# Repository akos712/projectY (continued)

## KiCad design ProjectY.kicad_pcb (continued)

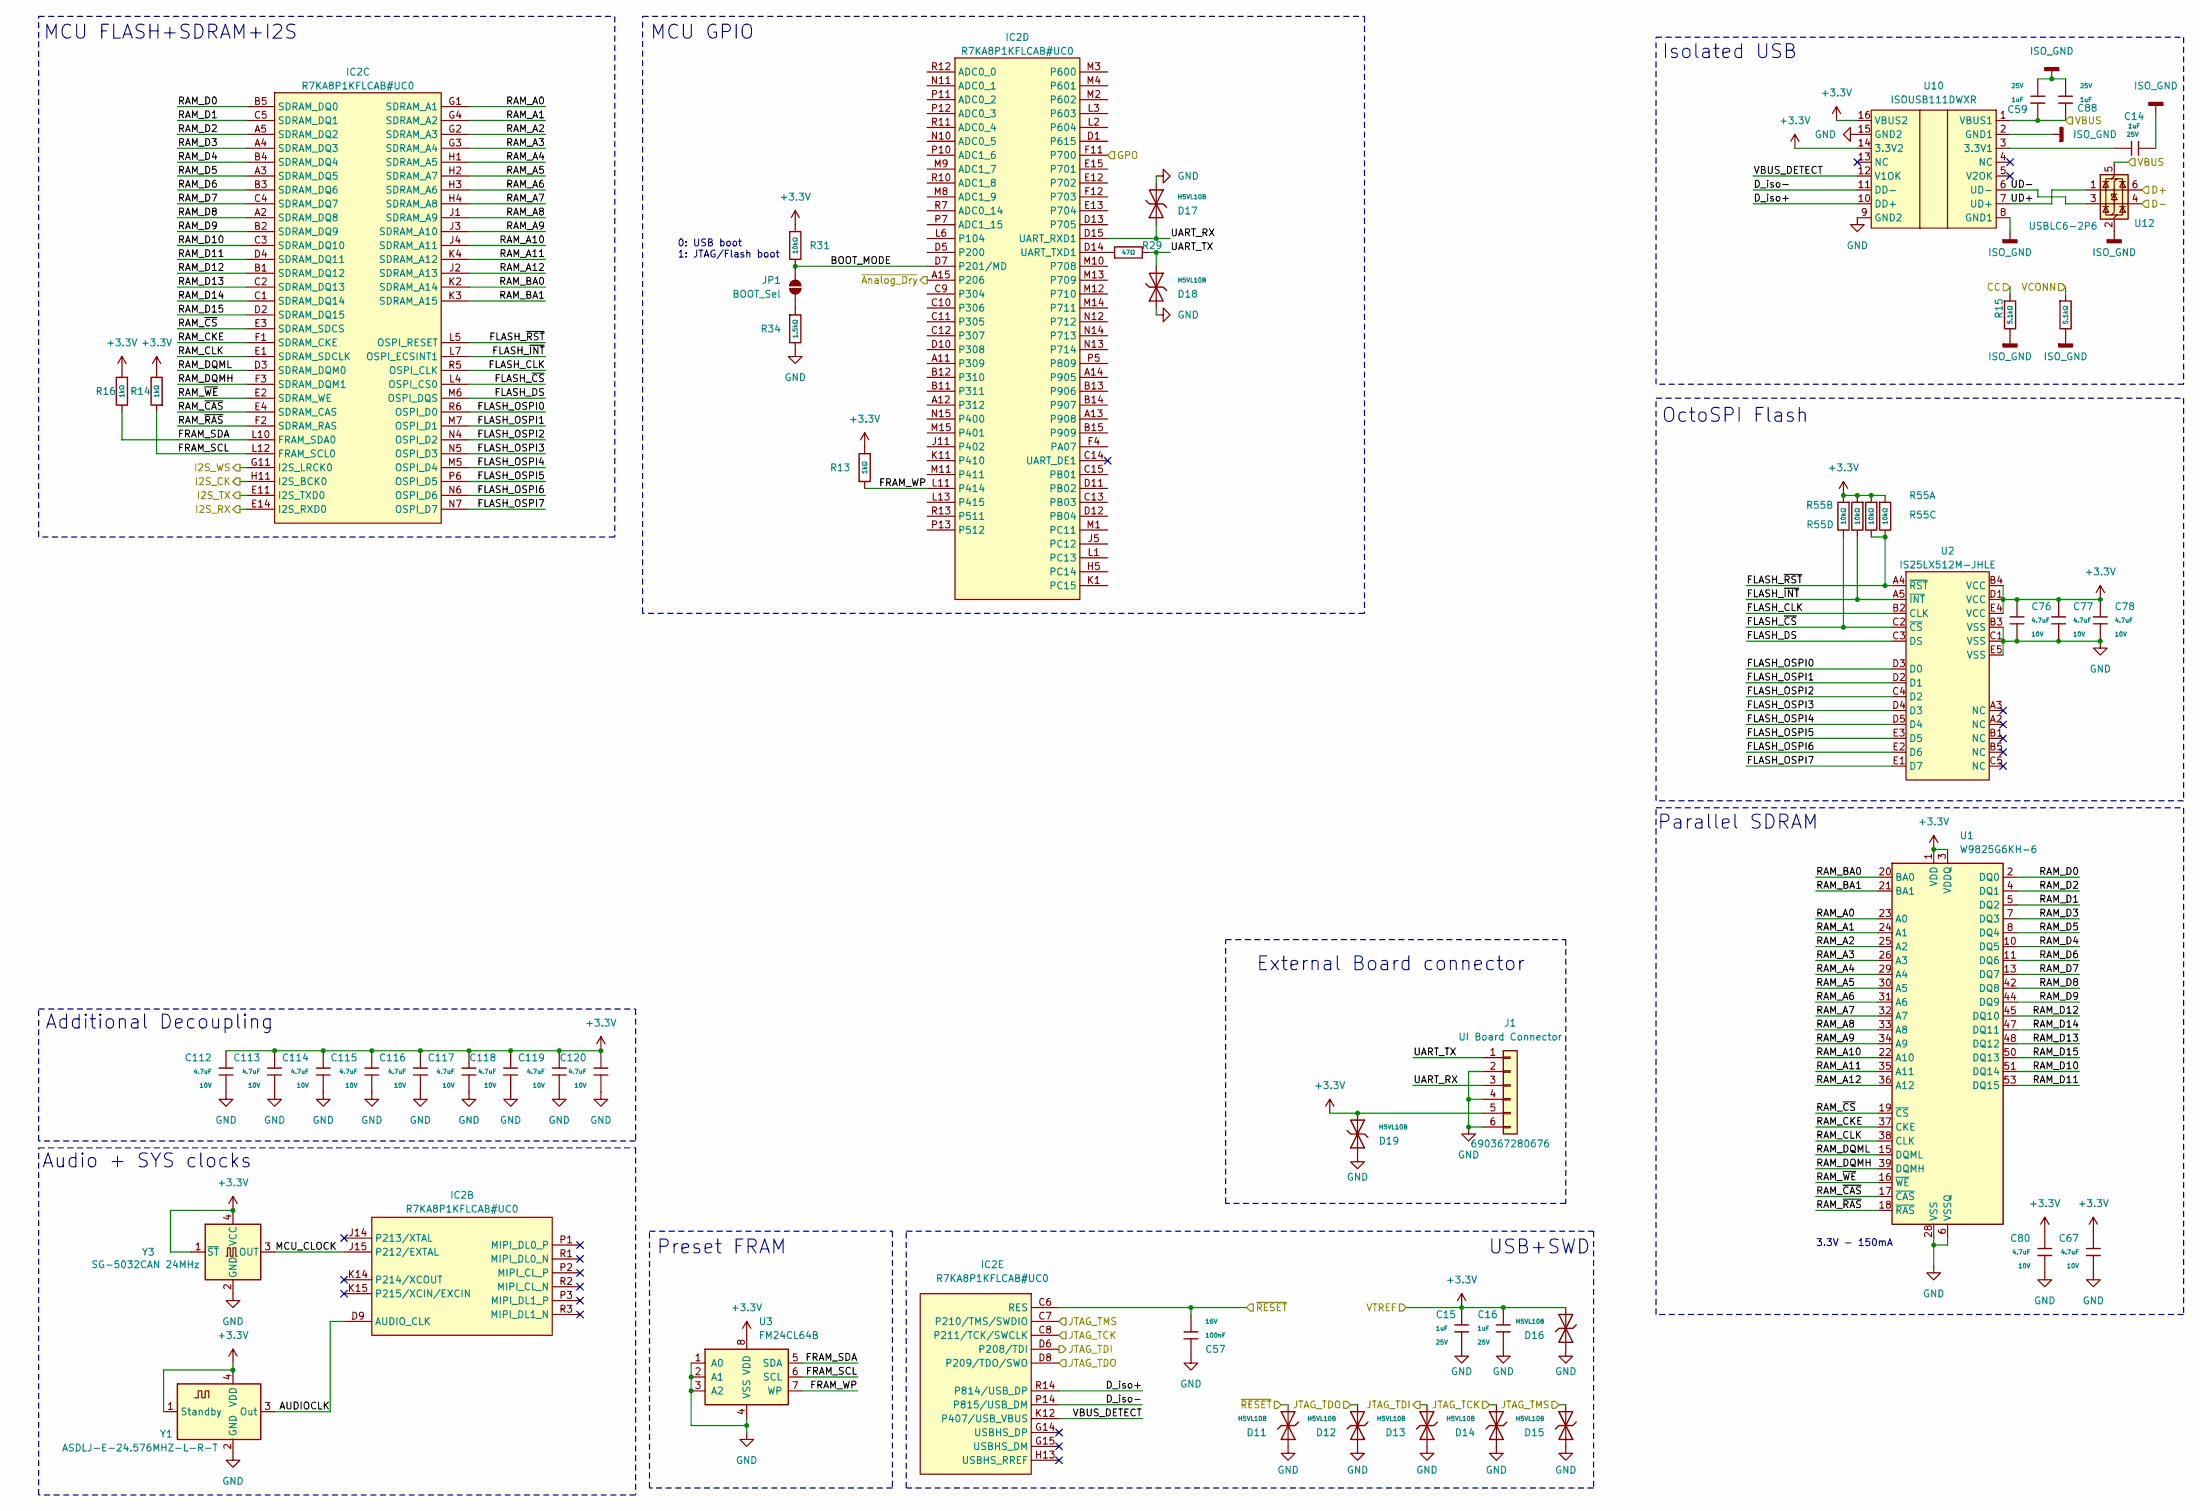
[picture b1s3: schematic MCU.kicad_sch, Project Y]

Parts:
C14, C15, C16, C59, C88: 1uF; C_0402; Voltage Rated 25V; Tolerance ±10%; Part CL05A105KA5NQNC; LCSC C52923
C57: 100nF; C_0402; Voltage Rated 16V; Tolerance ±10%; Part CL05B104KO5NNNC; LCSC C1525
C67, C76, C77, C78, C80, C112, C113, C114, C115, C116, C117, C118, C119, C120: 4.7uF; C_0402; Voltage Rated 10V; Tolerance ±20%; Part CL05A475MP5NRNC; LCSC C23733
D11, D12, D13, D14, D15, D16, D17, D18, D19: H5VL10B; D_DFN1006-2L; Clamping Voltage@Ipp 10V; Breakdown Voltage (VBR) 5.6V; Part H5VL10B; LCSC C7420372
IC2: R7KA8P1KFLCAB#UC0; BGA-225_15x15_11.0x11.0mm; Manufacturer_Part_Number R7KA8P1KFLCAB#UC0
J1: UI Board Connector; J_Wurth_WR-MM_690367280676
JP1: BOOT_Sel; SolderJumper-2_P1.3mm_Open_RoundedPad1.0x1.5mm
R1, R15: 5.1kΩ; R_0402; Overload Voltage (Max) 50V; Tolerance ±1%; Part 0402WGF5101TCE; LCSC C25905
R13, R14, R16: 1kΩ; R_0402; Overload Voltage (Max) 50V; Tolerance ±1%; Part 0402WGF1001TCE; LCSC C11702
R29: 47Ω; R_0402; Overload Voltage (Max) 50V; Tolerance ±1%; Part 0402WGF470JTCE; LCSC C25118
R31: 10kΩ; R_0402; Overload Voltage (Max) 50V; Tolerance ±1%; Part 0402WGF1002TCE; LCSC C25744
R34: 1.5kΩ; R_0402; Overload Voltage (Max) 50V; Tolerance ±1%; Part 0402WGF1501TCE; LCSC C25867
R55: 10kΩ; R_0402x4; Tolerance ±5%; Part 4D02WGJ0103TCE; LCSC C25725
U1: W9825G6KH-6; TSOP-II-54_22.2x10.16mm_P0.8mm; LCSC C97572
U2: IS25LX512M-JHLE; BGA-24_6x8mm_Layout5x5_P1.0mm
U3: FM24CL64B; SOIC-8_3.9x4.9mm_P1.27mm; LCSC C9829
U10: ISOUSB111DWXR; SOIC16_DW_TEX-L
U12: USBLC6-2P6; SOT-666
Y1: ASDLJ-E-24.576MHZ-L-R-T; Oscillator_SMD_Abracon_ASDMB-4Pin_2.5x2.0mm
Y3: SG-5032CAN 24MHz; Oscillator_SMD_SeikoEpson_SG8002LB-4Pin_5.0x3.2mm

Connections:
+3.3V: C15.2, C16.2, C67.1, C76.1, C77.1, C78.1, C80.1, C112.1, C113.1, C114.1, C115.1, C116.1, C117.1, C118.1, C119.1, C120.1, D16.1, D19.1, J1.5, R13.1, R14.2, R16.1, R31.1, R55.1, R55.2, R55.3, R55.4, U1.1 (VDD), U1.3 (VDDQ), U1.9 (VDDQ), U1.14 (VDD), U1.27 (VDD), U1.43 (VDDQ), U1.49 (VDDQ), U2.B4 (VCC), U2.D1 (VCC), U2.E4 (VCC), U3.8 (VDD), U10.14 (3.3V2), U10.16 (VBUS2), Y1.1 (Standby), Y1.4 (VDD), Y3.1 (~ST), Y3.4 (VCC); also elsewhere on the board
/Analog Audio/GP0: IC2.F11 (P700); also elsewhere on the board
/Analog Audio/I2S_CK: IC2.H11 (I2S_BCK0); also elsewhere on the board
/Analog Audio/I2S_RX: IC2.E14 (I2S_RXD0); also elsewhere on the board
/Analog Audio/I2S_TX: IC2.E11 (I2S_TXD0); also elsewhere on the board
/Analog Audio/I2S_WS: IC2.G11 (I2S_LRCK0); also elsewhere on the board
/Analog Audio/~Analog_Dry: IC2.A15 (P206); also elsewhere on the board
/DSP/AUDIOCLK: IC2.D9 (AUDIO_CLK), Y1.3 (Out)
/DSP/BOOT_MODE: IC2.D7 (P201/MD), JP1.2 (B), R31.2
/DSP/CC: R15.1; also elsewhere on the board
/DSP/D+: U12.6 (I/O1); also elsewhere on the board
/DSP/D-: U12.4 (I/O2); also elsewhere on the board
/DSP/D_iso+: IC2.R14 (P814/USB_DP), U10.10 (DD+)
/DSP/D_iso-: IC2.P14 (P815/USB_DM), U10.11 (DD-)
/DSP/FLASH_CLK: IC2.R5 (OSPI_CLK), U2.B2 (CLK)
/DSP/FLASH_DS: IC2.M6 (OSPI_DQS), U2.C3 (DS)
/DSP/FLASH_OSPI0: IC2.R6 (OSPI_D0), U2.D3 (D0)
/DSP/FLASH_OSPI1: IC2.M7 (OSPI_D1), U2.D2 (D1)
/DSP/FLASH_OSPI2: IC2.N4 (OSPI_D2), U2.C4 (D2)
/DSP/FLASH_OSPI3: IC2.N5 (OSPI_D3), U2.D4 (D3)
/DSP/FLASH_OSPI4: IC2.M5 (OSPI_D4), U2.D5 (D4)
/DSP/FLASH_OSPI5: IC2.P6 (OSPI_D5), U2.E3 (D5)
/DSP/FLASH_OSPI6: IC2.N6 (OSPI_D6), U2.E2 (D6)
/DSP/FLASH_OSPI7: IC2.N7 (OSPI_D7), U2.E1 (D7)
/DSP/FLASH_~CS: IC2.L4 (OSPI_CS0), R55.5, U2.C2 (~CS)
/DSP/FLASH_~INT: IC2.L7 (OSPI_ECSINT1), R55.8, U2.A5 (~INT)
/DSP/FLASH_~RST: IC2.L5 (OSPI_RESET), R55.6, R55.7, U2.A4 (~RST)
/DSP/FRAM_SCL: IC2.L12 (FRAM_SCL0), R14.1, U3.6 (SCL)
/DSP/FRAM_SDA: IC2.L10 (FRAM_SDA0), R16.2, U3.5 (SDA)
/DSP/FRAM_WP: IC2.L11 (P414), R13.2, U3.7 (WP)
/DSP/JTAG_TCK: D14.1, IC2.C8 (P211/TCK/SWCLK); also elsewhere on the board
/DSP/JTAG_TDI: D13.1, IC2.D6 (P208/TDI); also elsewhere on the board
/DSP/JTAG_TDO: D12.1, IC2.D8 (P209/TDO/SWO); also elsewhere on the board
/DSP/JTAG_TMS: D15.1, IC2.C7 (P210/TMS/SWDIO); also elsewhere on the board
/DSP/MCU_CLOCK: IC2.J15 (P212/EXTAL), Y3.3 (OUT)
/DSP/RAM_A0: IC2.G1 (SDRAM_A1), U1.23 (A0)
/DSP/RAM_A1: IC2.G4 (SDRAM_A2), U1.24 (A1)
/DSP/RAM_A2: IC2.G2 (SDRAM_A3), U1.25 (A2)
/DSP/RAM_A3: IC2.G3 (SDRAM_A4), U1.26 (A3)
/DSP/RAM_A4: IC2.H1 (SDRAM_A5), U1.29 (A4)
/DSP/RAM_A5: IC2.H2 (SDRAM_A7), U1.30 (A5)
/DSP/RAM_A6: IC2.H3 (SDRAM_A6), U1.31 (A6)
/DSP/RAM_A7: IC2.H4 (SDRAM_A8), U1.32 (A7)
/DSP/RAM_A8: IC2.J1 (SDRAM_A9), U1.33 (A8)
/DSP/RAM_A9: IC2.J3 (SDRAM_A10), U1.34 (A9)
/DSP/RAM_A10: IC2.J4 (SDRAM_A11), U1.22 (A10)
/DSP/RAM_A11: IC2.K4 (SDRAM_A12), U1.35 (A11)
/DSP/RAM_A12: IC2.J2 (SDRAM_A13), U1.36 (A12)
/DSP/RAM_BA0: IC2.K2 (SDRAM_A14), U1.20 (BA0)
/DSP/RAM_BA1: IC2.K3 (SDRAM_A15), U1.21 (BA1)
/DSP/RAM_CKE: IC2.F1 (SDRAM_CKE), U1.37 (CKE)
/DSP/RAM_CLK: IC2.E1 (SDRAM_SDCLK), U1.38 (CLK)
/DSP/RAM_D0: IC2.B5 (SDRAM_DQ0), U1.2 (DQ0)
/DSP/RAM_D1: IC2.C5 (SDRAM_DQ1), U1.5 (DQ2)
/DSP/RAM_D2: IC2.A5 (SDRAM_DQ2), U1.4 (DQ1)
/DSP/RAM_D3: IC2.A4 (SDRAM_DQ3), U1.7 (DQ3)
/DSP/RAM_D4: IC2.B4 (SDRAM_DQ4), U1.10 (DQ5)
/DSP/RAM_D5: IC2.A3 (SDRAM_DQ5), U1.8 (DQ4)
/DSP/RAM_D6: IC2.B3 (SDRAM_DQ6), U1.11 (DQ6)
/DSP/RAM_D7: IC2.C4 (SDRAM_DQ7), U1.13 (DQ7)
/DSP/RAM_D8: IC2.A2 (SDRAM_DQ8), U1.42 (DQ8)
/DSP/RAM_D9: IC2.B2 (SDRAM_DQ9), U1.44 (DQ9)
/DSP/RAM_D10: IC2.C3 (SDRAM_DQ10), U1.51 (DQ14)
/DSP/RAM_D11: IC2.D4 (SDRAM_DQ11), U1.53 (DQ15)
/DSP/RAM_D12: IC2.B1 (SDRAM_DQ12), U1.45 (DQ10)
/DSP/RAM_D13: IC2.C2 (SDRAM_DQ13), U1.48 (DQ12)
/DSP/RAM_D14: IC2.C1 (SDRAM_DQ14), U1.47 (DQ11)
/DSP/RAM_D15: IC2.D2 (SDRAM_DQ15), U1.50 (DQ13)
/DSP/RAM_DQMH: IC2.F3 (SDRAM_DQM1), U1.39 (DQMH)
/DSP/RAM_DQML: IC2.D3 (SDRAM_DQM0), U1.15 (DQML)
/DSP/RAM_~CAS: IC2.E4 (SDRAM_CAS), U1.17 (~CAS)
/DSP/RAM_~CS: IC2.E3 (SDRAM_SDCS), U1.19 (~CS)
/DSP/RAM_~RAS: IC2.F2 (SDRAM_RAS), U1.18 (~RAS)
/DSP/RAM_~WE: IC2.E2 (SDRAM_WE), U1.16 (~WE)
/DSP/UART_RX: D17.2, IC2.D15 (UART_RXD1), J1.3
/DSP/UART_TX: D18.1, J1.1, R29.2
/DSP/UD+: U10.7 (UD+), U12.1 (I/O1)
/DSP/UD-: U10.6 (UD-), U12.3 (I/O2)
/DSP/VBUS: C59.1, C88.1, U10.1 (VBUS1), U12.5 (VBUS); also elsewhere on the board
/DSP/VBUS_DETECT: IC2.K12 (P407/USB_VBUS), U10.12 (V1OK)
/DSP/VCONN: R1.1; also elsewhere on the board
/DSP/~RESET: C57.2, D11.1, IC2.C6 (RES); also elsewhere on the board
GND: C15.1, C16.1, C57.1, C67.2, C76.2, C77.2, C78.2, C80.2, C112.2, C113.2, C114.2, C115.2, C116.2, C117.2, C118.2, C119.2, C120.2, D11.2, D12.2, D13.2, D14.2, D15.2, D16.2, D17.1, D18.2, D19.2, J1.2, J1.4, J1.6, R34.2, U1.6 (VSSQ), U1.12 (VSSQ), U1.28 (VSS), U1.41 (VSS), U1.46 (VSSQ), U1.52 (VSSQ), U1.54 (VSS), U2.B3 (VSS), U2.C1 (VSS), U2.E5 (VSS), U3.1 (A0), U3.2 (A1), U3.3 (A2), U3.4 (VSS), U10.9 (GND2), U10.15 (GND2), Y1.2 (GND), Y3.2 (GND); also elsewhere on the board
ISO_GND: C14.2, C59.2, C88.2, R1.2, R15.2, U10.2 (GND1), U10.8 (GND1), U12.2 (GND); also elsewhere on the board
unnamed: IC2.D14 (UART_TXD1), R29.1
unnamed: JP1.1 (A), R34.1
unnamed: C14.1, U10.3 (3.3V1)

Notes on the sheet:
OctoSPI Flash
Isolated USB
MCU GPIO
Parallel SDRAM
MCU FLASH+SDRAM+I2S
3.3V - 150mA
0: USB boot 1: JTAG/Flash boot
External Board connector
Audio + SYS clocks
USB+SWD
Preset FRAM
Additional Decoupling

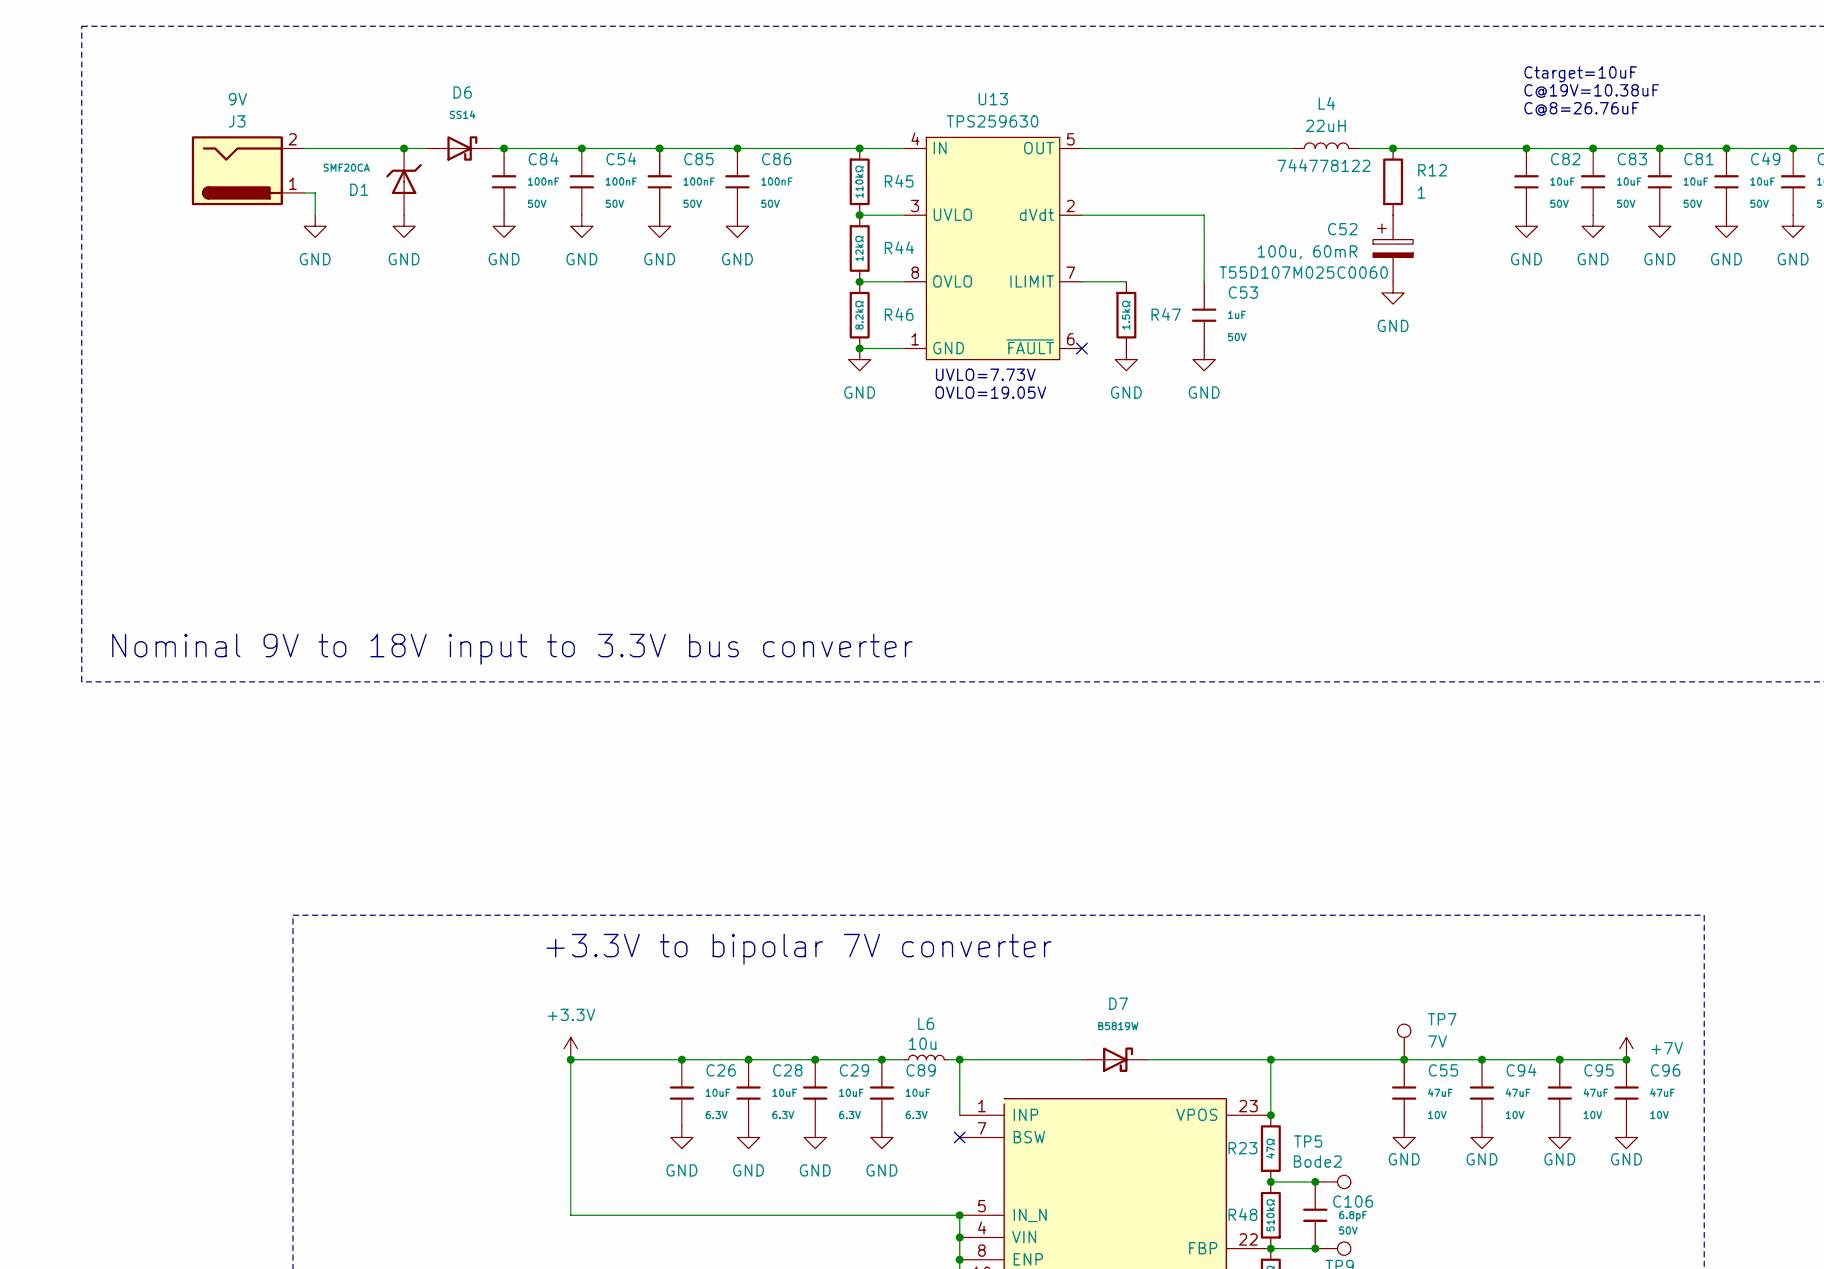
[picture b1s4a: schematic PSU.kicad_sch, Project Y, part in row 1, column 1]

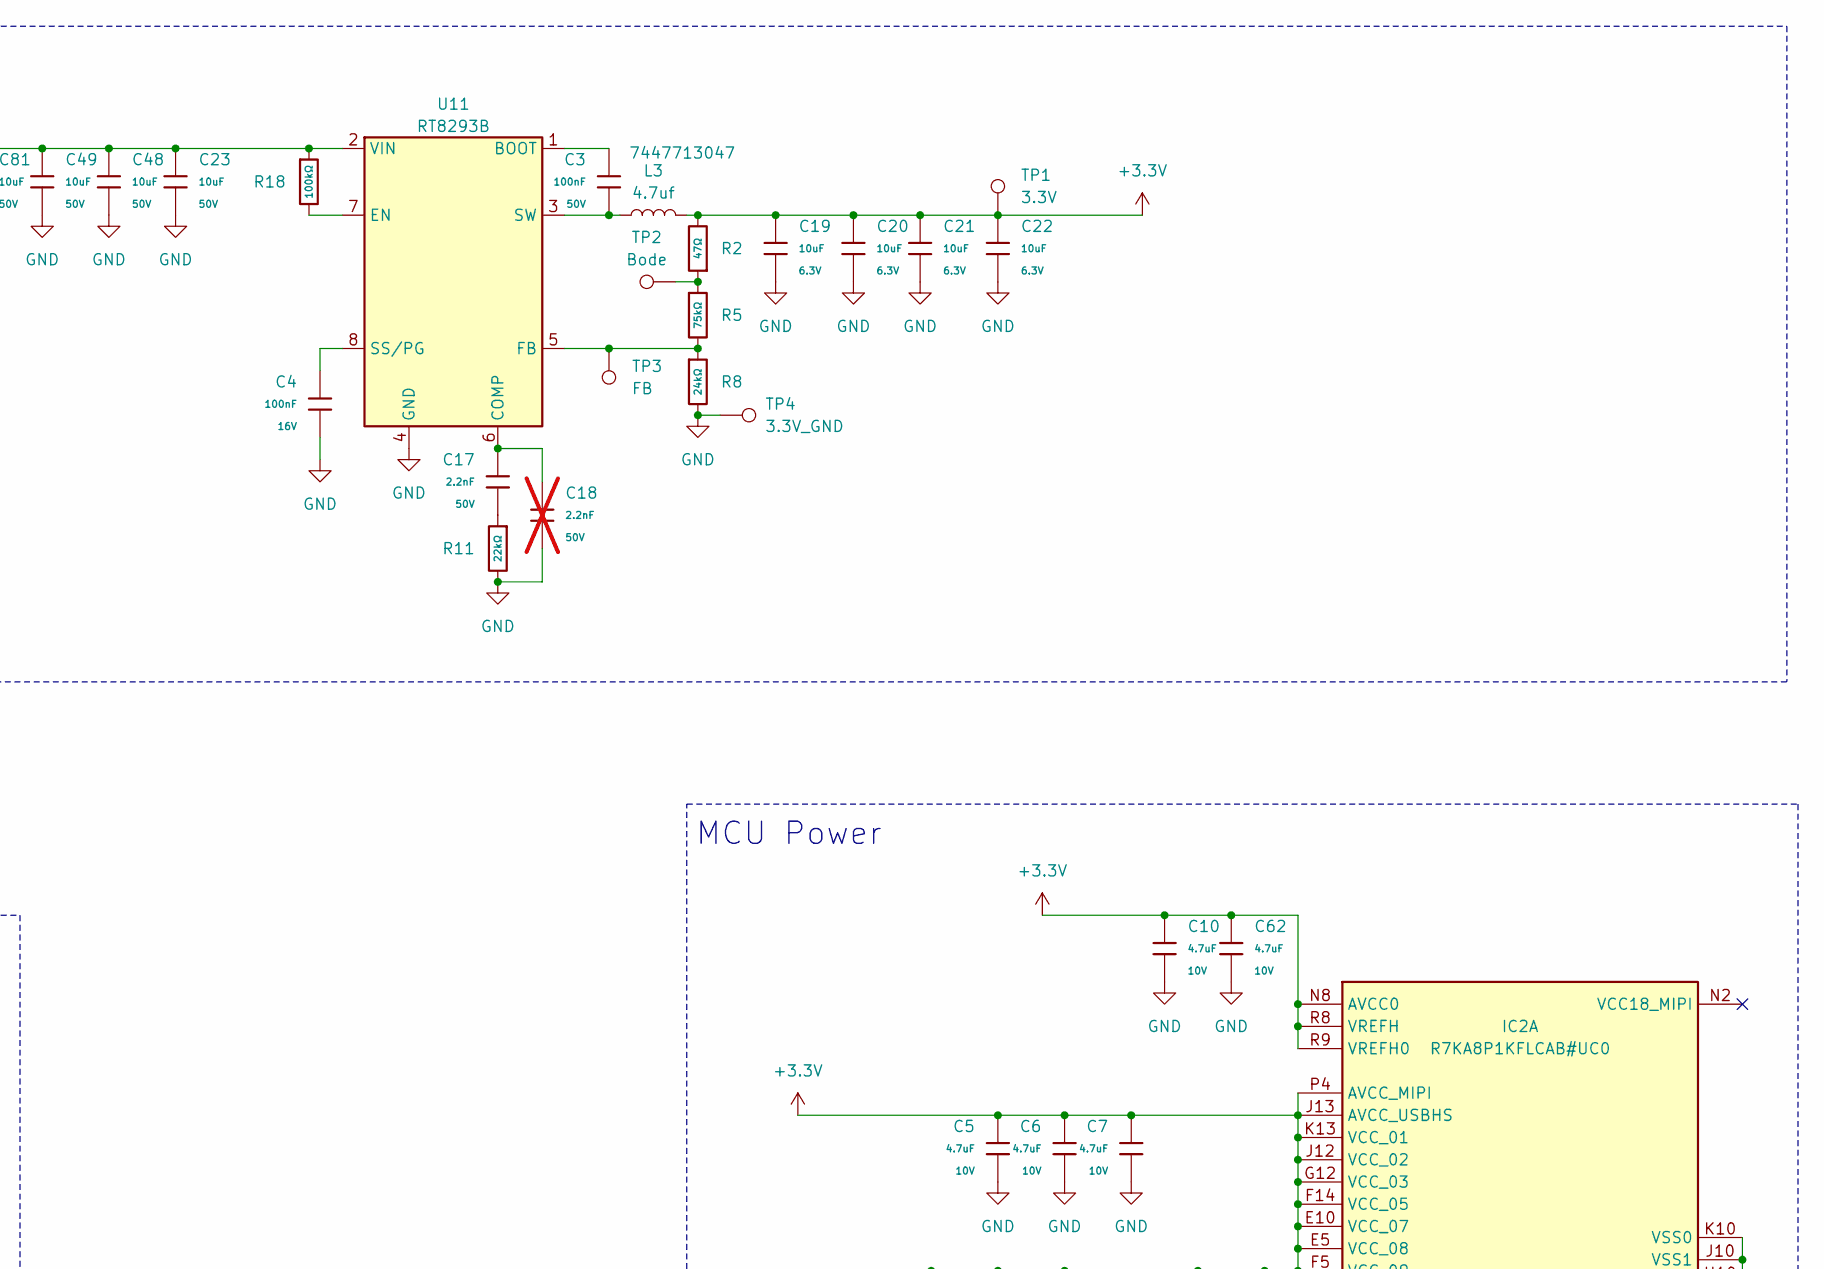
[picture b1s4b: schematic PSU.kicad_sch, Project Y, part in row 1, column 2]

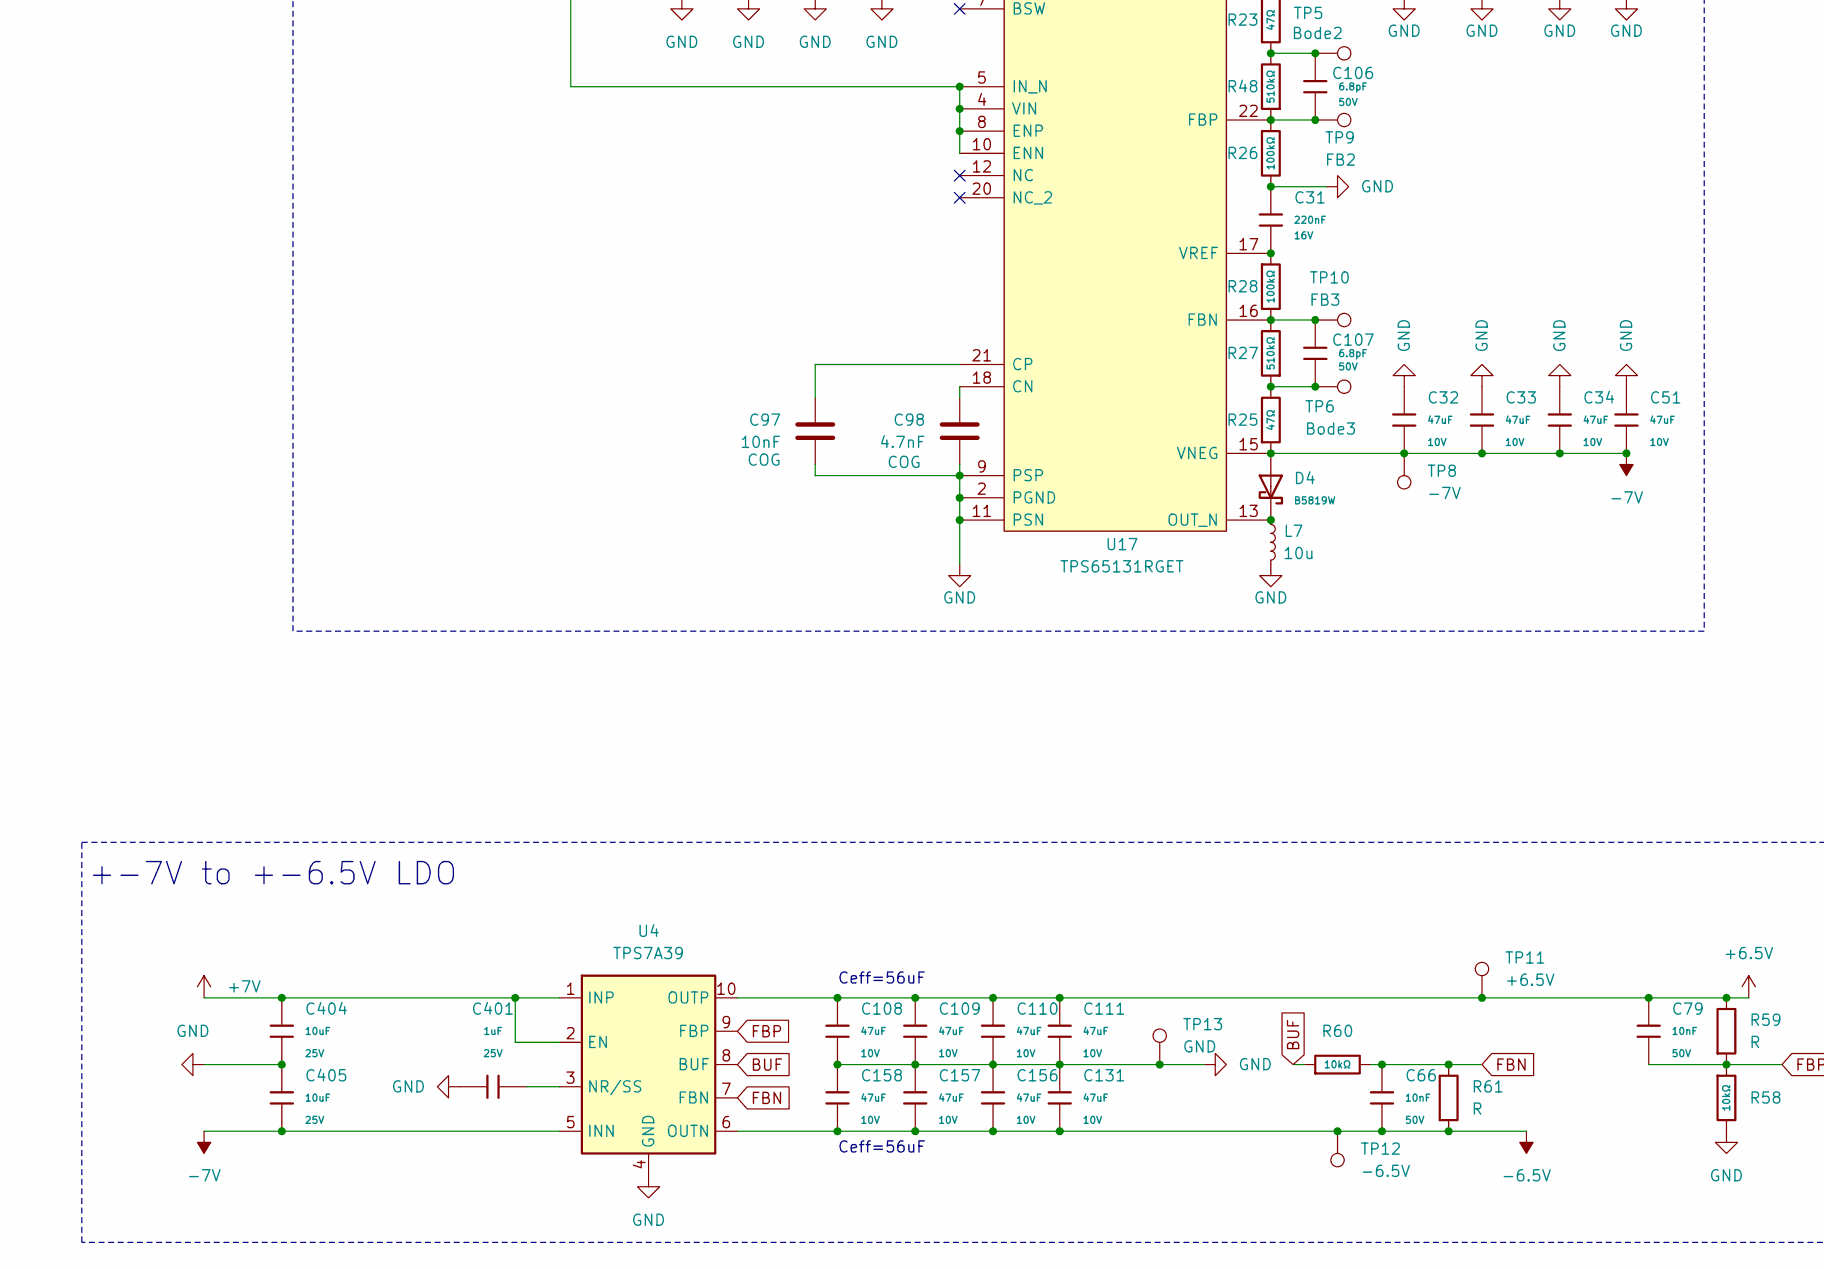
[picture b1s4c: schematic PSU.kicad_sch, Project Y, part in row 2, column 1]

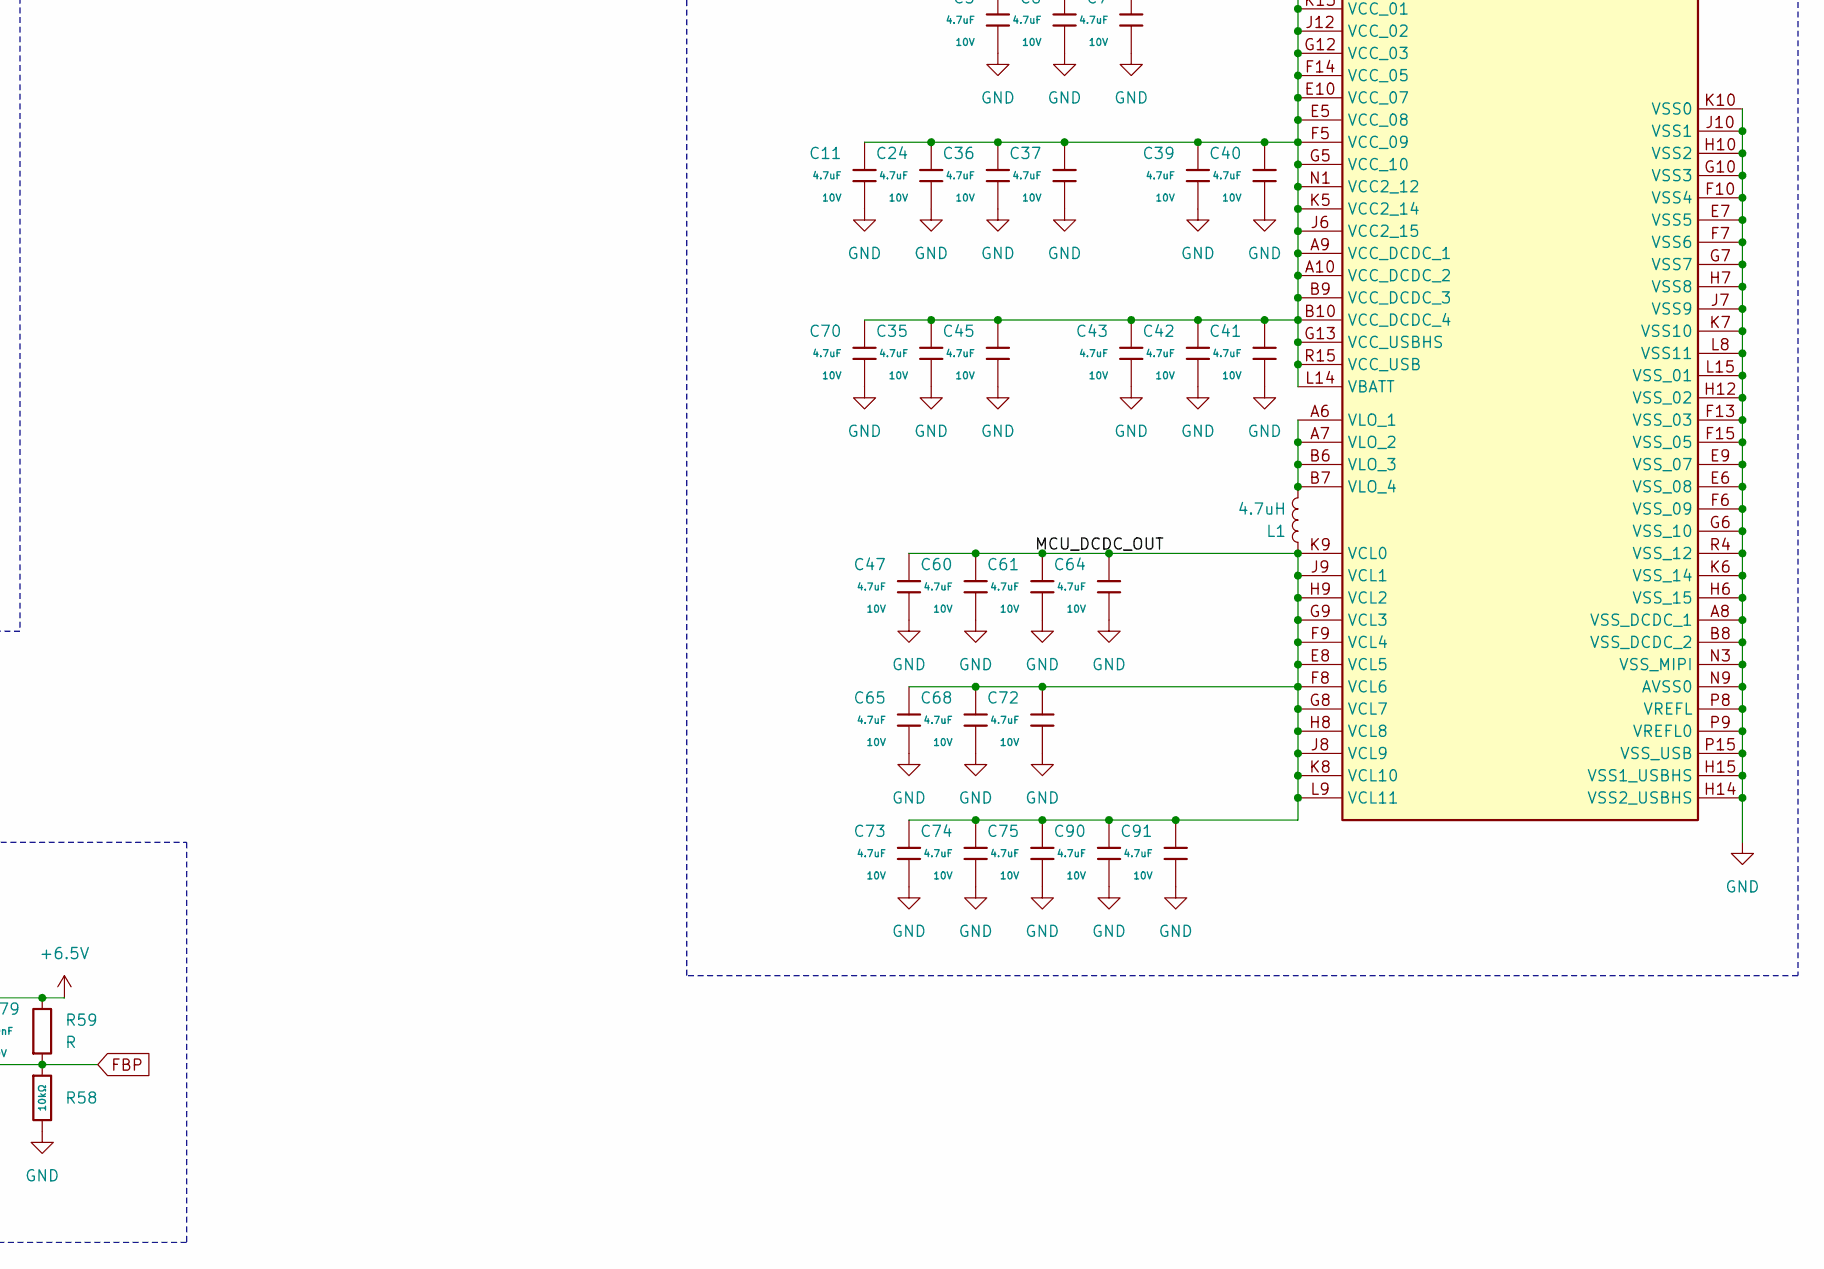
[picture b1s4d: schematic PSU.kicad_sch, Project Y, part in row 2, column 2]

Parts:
C3, C54, C84, C85, C86: 100nF; C_0402; Voltage Rated 50V; Tolerance ±10%; Part CL05B104KB54PNC; LCSC C307331
C4: 100nF; C_0402; Voltage Rated 16V; Tolerance ±10%; Part CL05B104KO5NNNC; LCSC C1525
C5, C6, C7, C10, C11, C24, C35, C36, C37, C39, C40, C41, C42, C43, C45, C47, C60, C61, C62, C64, C65, C68, C70, C72, C73, C74, C75, C90, C91: 4.7uF; C_0402; Voltage Rated 10V; Tolerance ±20%; Part CL05A475MP5NRNC; LCSC C23733
C17: 2.2nF; C_0805; Voltage Rated 50V; Tolerance ±5%; Part CL21C222JBFNNNE; LCSC C28260
C18: 2.2nF; C_0805; Voltage Rated 50V; Tolerance ±5%; Part CL21C222JBFNNNE; LCSC C28260; not fitted
C19, C20, C21, C22, C26, C28, C29, C89: 10uF; C_0402; Voltage Rated 6.3V; Tolerance ±20%; Part CL05A106MQ5NUNC; LCSC C15525
C23, C48, C49, C81, C82, C83: 10uF; C_0805; Voltage Rated 50V; Tolerance ±10%; Part GRM21BR61H106KE43L; LCSC C440198
C31: 220nF; C_0402; Voltage Rated 16V; Tolerance ±10%; Part CL05B224KO5NNNC; LCSC C16772
C32, C33, C34, C51, C55, C94, C95, C96, C108, C109, C110, C111, C131, C156, C157, C158: 47uF; C_1206; Voltage Rated 10V; Tolerance ±20%; Part CL31A476MPHNNNE; LCSC C96123
C52: 100u, 60mR; CP_EIA-7343-31_Kemet-D
C53: 1uF; C_0603; Voltage Rated 50V; Tolerance ±10%; Part CL10A105KB8NNNC; LCSC C15849
C66, C79: 10nF; C_0402; Voltage Rated 50V; Tolerance ±10%; Part CL05B103KB5NNNC; LCSC C15195
C97: 10nF; C_0603_1608Metric
C98: 4.7nF; C_0603_1608Metric
C106, C107: 6.8pF; C_0402; Voltage Rated 50V; Part 0402CG6R8C500NT; LCSC C1576
C401: 1uF; C_0402; Voltage Rated 25V; Tolerance ±10%; Part CL05A105KA5NQNC; LCSC C52923
C404, C405: 10uF; C_0603; Voltage Rated 25V; Tolerance ±20%; Part CL10A106MA8NRNC; LCSC C96446
D1: SMF20CA; D_SOD-123FL; Clamping Voltage 32.4V; Voltage - Breakdown 24.5V; Part SMF20CA; LCSC C42371747
D4, D7: B5819W; D_SOD-123; Forward Voltage (Vf@If) 900mV@3A; Reverse Voltage (Vr) 40V; Part B5819W; LCSC C64885
D6: SS14; D_SMA; Forward Voltage (Vf@If) 550mV@1A; Reverse Voltage (Vr) 40V; Part SS14; LCSC C2480
IC2: R7KA8P1KFLCAB#UC0; BGA-225_15x15_11.0x11.0mm; Manufacturer_Part_Number R7KA8P1KFLCAB#UC0
J3: 9V; BarrelJack_GCT_DCJ200-10-A_Horizontal
L1: 4.7uH; L_Wuerth_MAPI-4030
L3: 4.7uf; WE-PD_1030P
L4: 22uH; L_7.3x7.3_H3.5
L6, L7: 10u; L_Sunlord_MWSA0518S; LCSC Part # C139506
R2, R23, R25: 47Ω; R_0402; Overload Voltage (Max) 50V; Tolerance ±1%; Part 0402WGF470JTCE; LCSC C25118
R5: 75kΩ; R_0402; Overload Voltage (Max) 50V; Tolerance ±1%; Part 0402WGF7502TCE; LCSC C25798
R8: 24kΩ; R_0402; Overload Voltage (Max) 50V; Tolerance ±1%; Part 0402WGF2402TCE; LCSC C25769
R11: 22kΩ; R_0805; Overload Voltage (Max) 150V; Tolerance ±1%; Part 0805W8F2202T5E; LCSC C17560
R12: 1; R_0402
R18, R26, R28: 100kΩ; R_0402; Overload Voltage (Max) 50V; Tolerance ±1%; Part 0402WGF1003TCE; LCSC C25741
R27, R48: 510kΩ; R_0402; Overload Voltage (Max) 50V; Tolerance ±1%; Part 0402WGF5103TCE; LCSC C11616
R44: 12kΩ; R_0402; Overload Voltage (Max) 50V; Tolerance ±1%; Part 0402WGF1202TCE; LCSC C25752
R45: 110kΩ; R_0603; Overload Voltage (Max) 75V; Tolerance ±1%; Part 0603WAF1103T5E; LCSC C25805
R46: 8.2kΩ; R_0603; Overload Voltage (Max) 75V; Tolerance ±1%; Part 0603WAF8201T5E; LCSC C25981
R47: 1.5kΩ; R_0402; Overload Voltage (Max) 50V; Tolerance ±1%; Part 0402WGF1501TCE; LCSC C25867
R58, R60: 10kΩ; R_0402; Overload Voltage (Max) 50V; Tolerance ±1%; Part 0402WGF1002TCE; LCSC C25744
R59, R61: R; R_0402_1005Metric
TP1: 3.3V; GEN_TP_PCB
TP2: Bode; GEN_TP_PCB
TP3: FB; GEN_TP_PCB
TP4: 3.3V_GND; TestPoint_Pad_1.0x1.0mm
TP5: Bode2; GEN_TP_PCB
TP6: Bode3; GEN_TP_PCB
TP7: 7V; GEN_TP_PCB
TP8: -7V; GEN_TP_PCB
TP9: FB2; GEN_TP_PCB
TP10: FB3; GEN_TP_PCB
TP11: +6.5V; TestPoint_Pad_1.0x1.0mm
TP12: -6.5V; TestPoint_Pad_1.0x1.0mm
TP13: GND; TestPoint_Pad_1.0x1.0mm
U4: TPS7A39; Texas_S-PVSON-N10_ThermalVias; LCSC C2685819
U11: RT8293B; SOP-8-1EP_4.57x4.57mm_P1.27mm_EP4.57x4.45mm_ThermalVias
U13: TPS259630; TI_SO-PowerPAD-8
U17: TPS65131RGET; VQFN-24-1EP_4x4mm_P0.5mm_EP2.5x2.5mm_ThermalVias; Mouser2 Part Number 595-TPS65131RGET

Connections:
+3.3V: C5.1, C6.1, C7.1, C10.1, C11.1, C19.1, C20.1, C21.1, C22.1, C24.1, C26.1, C28.1, C29.1, C35.1, C36.1, C37.1, C39.1, C40.1, C41.1, C42.1, C43.1, C45.1, C62.1, C70.1, C89.1, IC2.A9 (VCC_DCDC_1), IC2.A10 (VCC_DCDC_2), IC2.B9 (VCC_DCDC_3), IC2.B10 (VCC_DCDC_4), IC2.E5 (VCC_08), IC2.E10 (VCC_07), IC2.F5 (VCC_09), IC2.F14 (VCC_05), IC2.G5 (VCC_10), IC2.G12 (VCC_03), IC2.G13 (VCC_USBHS), IC2.J6 (VCC2_15), IC2.J12 (VCC_02), IC2.J13 (AVCC_USBHS), IC2.K5 (VCC2_14), IC2.K13 (VCC_01), IC2.L14 (VBATT), IC2.N1 (VCC2_12), IC2.N8 (AVCC0), IC2.P4 (AVCC_MIPI), IC2.R8 (VREFH), IC2.R9 (VREFH0), IC2.R15 (VCC_USB), L3.2, L6.1, R2.2, TP1.1, U17.4 (VIN), U17.5 (IN_N), U17.6 (IN_N_2), U17.8 (ENP), U17.10 (ENN); also elsewhere on the board
+6.5V: C79.1, C108.1, C109.1, C110.1, C111.1, R59.1, TP11.1, U4.10 (OUTP); also elsewhere on the board
+7V: C55.1, C94.1, C95.1, C96.1, C404.1, D7.1, R23.2, TP7.1, U4.1 (INP), U4.2 (EN), U17.23 (VPOS)
-6.5V: C66.2, C131.2, C156.2, C157.2, C158.2, R61.2, TP12.1, U4.6 (OUTN); also elsewhere on the board
-7V: C32.2, C33.2, C34.2, C51.2, C405.2, D4.2, R25.1, TP8.1, U4.5 (INN), U17.15 (VNEG)
/PSU/MCU_DCDC_OUT: C47.1, C60.1, C61.1, C64.1, C65.1, C68.1, C72.1, C73.1, C74.1, C75.1, C90.1, C91.1, IC2.E8 (VCL5), IC2.F8 (VCL6), IC2.F9 (VCL4), IC2.G8 (VCL7), IC2.G9 (VCL3), IC2.H8 (VCL8), IC2.H9 (VCL2), IC2.J8 (VCL9), IC2.J9 (VCL1), IC2.K8 (VCL10), IC2.K9 (VCL0), IC2.L9 (VCL11), L1.1
BUF: R60.1, U4.8 (BUF)
FBN: C66.1, R60.2, R61.1, U4.7 (FBN)
FBP: C79.2, R58.1, R59.2, U4.9 (FBP)
GND: C4.2, C5.2, C6.2, C7.2, C10.2, C11.2, C18.2, C19.2, C20.2, C21.2, C22.2, C23.2, C24.2, C26.2, C28.2, C29.2, C31.1, C32.1, C33.1, C34.1, C35.2, C36.2, C37.2, C39.2, C40.2, C41.2, C42.2, C43.2, C45.2, C47.2, C48.2, C49.2, C51.1, C52.2, C53.2, C54.2, C55.2, C60.2, C61.2, C62.2, C64.2, C65.2, C68.2, C70.2, C72.2, C73.2, C74.2, C75.2, C81.2, C82.2, C83.2, C84.2, C85.2, C86.2, C89.2, C90.2, C91.2, C94.2, C95.2, C96.2, C97.2, C98.2, C108.2, C109.2, C110.2, C111.2, C131.1, C156.1, C157.1, C158.1, C401.1, C404.2, C405.1, D1.2, IC2.A8 (VSS_DCDC_1), IC2.B8 (VSS_DCDC_2), IC2.E6 (VSS_08), IC2.E7 (VSS5), IC2.E9 (VSS_07), IC2.F6 (VSS_09), IC2.F7 (VSS6), IC2.F10 (VSS4), IC2.F13 (VSS_03), IC2.F15 (VSS_05), IC2.G6 (VSS_10), IC2.G7 (VSS7), IC2.G10 (VSS3), IC2.H6 (VSS_15), IC2.H7 (VSS8), IC2.H10 (VSS2), IC2.H12 (VSS_02), IC2.H14 (VSS2_USBHS), IC2.H15 (VSS1_USBHS), IC2.J7 (VSS9), IC2.J10 (VSS1), IC2.K6 (VSS_14), IC2.K7 (VSS10), IC2.K10 (VSS0), IC2.L8 (VSS11), IC2.L15 (VSS_01), IC2.N3 (VSS_MIPI), IC2.N9 (AVSS0), IC2.P8 (VREFL), IC2.P9 (VREFL0), IC2.P15 (VSS_USB), IC2.R4 (VSS_12), J3.1, L7.2, R8.2, R11.2, R26.2, R46.2, R47.2, R58.2, TP4.1, TP13.1, U4.4 (GND), U4.11 (GND), U11.4 (GND), U11.9 (GND), U13.1 (GND), U13.9 (EPAD), U17.2 (PGND), U17.3 (PGND_2), U17.9 (PSP), U17.11 (PSN), U17.19 (AGND), U17.25 (POWERPAD); also elsewhere on the board
unnamed: C17.2, R11.1
unnamed: C52.1, R12.2
unnamed: C106.1, R23.1, R48.2, TP5.1
unnamed: C107.2, R25.2, R27.1, TP6.1
unnamed: D1.1, D6.2, J3.2
unnamed: IC2.A6 (VLO_1), IC2.A7 (VLO_2), IC2.B6 (VLO_3), IC2.B7 (VLO_4), L1.2
unnamed: R2.1, R5.1, TP2.1
unnamed: C401.2, U4.3 (NR/SS)
unnamed: C3.1, U11.1 (BOOT)
unnamed: C17.1, C18.1, U11.6 (COMP)
unnamed: R18.2, U11.7 (EN)
unnamed: R5.2, R8.1, TP3.1, U11.5 (FB)
unnamed: C4.1, U11.8 (SS/PG)
unnamed: C3.2, L3.1, U11.3 (SW)
unnamed: C23.1, C48.1, C49.1, C81.1, C82.1, C83.1, L4.2, R12.1, R18.1, U11.2 (VIN)
unnamed: R47.1, U13.7 (ILIMIT)
unnamed: C54.1, C84.1, C85.1, C86.1, D6.1, R45.1, U13.4 (IN)
unnamed: L4.1, U13.5 (OUT)
unnamed: R44.2, R46.1, U13.8 (OVLO)
unnamed: R44.1, R45.2, U13.3 (UVLO)
unnamed: C53.1, U13.2 (dVdt)
unnamed: C98.1, U17.18 (CN)
unnamed: C97.1, U17.21 (CP)
unnamed: C107.1, R27.2, R28.2, TP10.1, U17.16 (FBN)
unnamed: C106.2, R26.1, R48.1, TP9.1, U17.22 (FBP)
unnamed: D7.2, L6.2, U17.1 (INP), U17.24 (INP_2)
unnamed: D4.1, L7.1, U17.13 (OUT_N), U17.14 (OUT_N_2)
unnamed: C31.2, R28.1, U17.17 (VREF)

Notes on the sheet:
UVLO=7.73V OVLO=19.05V
MCU Power
+3.3V to bipolar 7V converter
Nominal 9V to 18V input to 3.3V bus converter
+-7V to +-6.5V LDO
Ceff=56uF
Ctarget=10uF C@19V=10.38uF C@8=26.76uF
